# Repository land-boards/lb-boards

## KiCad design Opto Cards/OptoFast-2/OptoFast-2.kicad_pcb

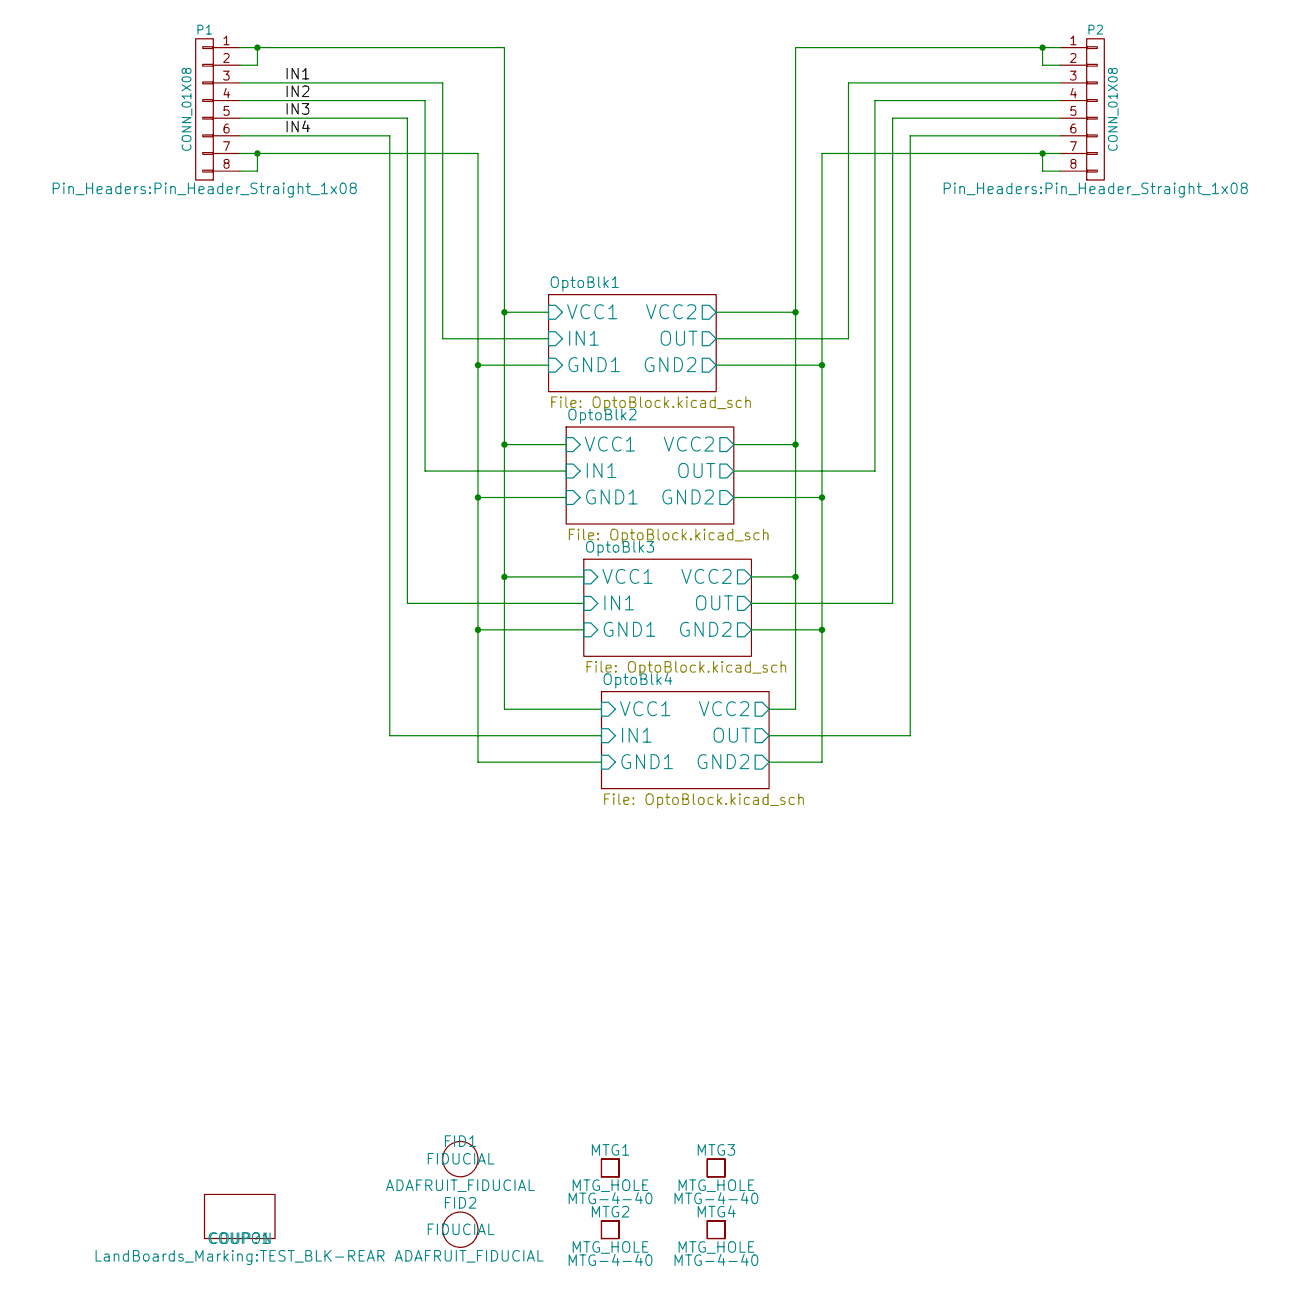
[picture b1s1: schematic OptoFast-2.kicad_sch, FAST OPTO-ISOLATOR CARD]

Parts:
COUP?1: COUPON; TEST_BLK-REAR
FID1, FID2: ADAFRUIT_FIDUCIAL; FIDUCIAL
MTG1, MTG2, MTG3, MTG4: MTG_HOLE; MTG-4-40
P1, P2: CONN_01X08; Pin_Header_Straight_1x08

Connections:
/IN1: P1.3; also elsewhere on the board
/IN2: P1.4; also elsewhere on the board
/IN3: P1.5; also elsewhere on the board
/IN4: P1.6; also elsewhere on the board
/OptoBlk1/GND1: P1.7, P1.8; also elsewhere on the board
/OptoBlk1/GND2: P2.7, P2.8; also elsewhere on the board
/OptoBlk1/OUT: P2.3; also elsewhere on the board
/OptoBlk1/VCC1: P1.1, P1.2; also elsewhere on the board
/OptoBlk1/VCC2: P2.1, P2.2; also elsewhere on the board
/OptoBlk2/OUT: P2.4; also elsewhere on the board
/OptoBlk3/OUT: P2.5; also elsewhere on the board
/OptoBlk4/OUT: P2.6; also elsewhere on the board

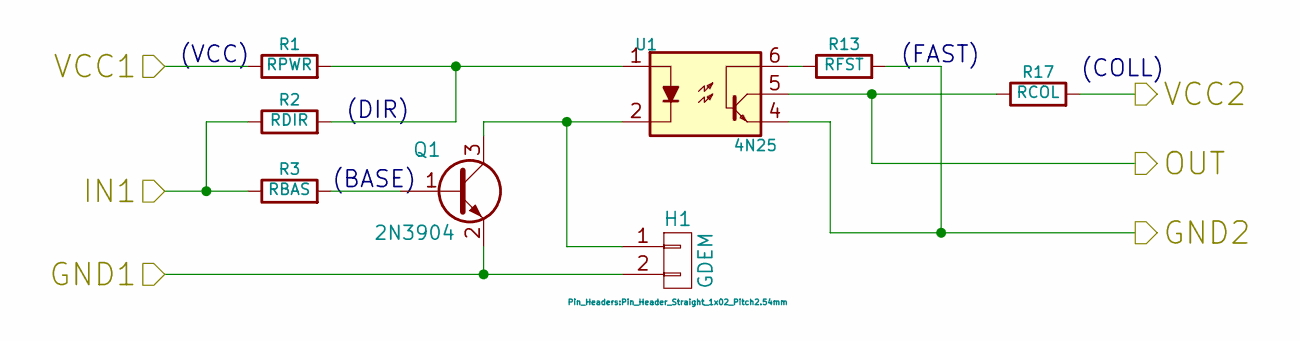
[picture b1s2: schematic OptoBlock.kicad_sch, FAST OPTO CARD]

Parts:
H1: GDEM; Pin_Header_Straight_1x02_Pitch2.54mm
Q1: 2N3904; SOT-23_Handsoldering
R1: RPWR; R_0805_HandSoldering
R2: RDIR; R_0805_HandSoldering
R3: RBAS; R_0805_HandSoldering
R13: RFST; R_0805_HandSoldering
R17: RCOL; R_0805_HandSoldering
U1: 4N25; DIP-6_W7.62mm_LongPads

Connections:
/IN1: R2.1, R3.1; also elsewhere on the board
/OptoBlk1/GND1: H1.2, Q1.2 (E); also elsewhere on the board
/OptoBlk1/GND2: R13.2, U1.4; also elsewhere on the board
/OptoBlk1/OUT: R17.1, U1.5; also elsewhere on the board
/OptoBlk1/VCC1: R1.1; also elsewhere on the board
/OptoBlk1/VCC2: R17.2; also elsewhere on the board
unnamed: H1.1, Q1.3 (C), U1.2
unnamed: Q1.1 (B), R3.2
unnamed: R1.2, R2.2, U1.1
unnamed: R13.1, U1.6

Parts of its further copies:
H2, H3, H4: GDEM; Pin_Header_Straight_1x02_Pitch2.54mm
Q2, Q3, Q4: 2N3904; SOT-23_Handsoldering
R4, R7, R10: RPWR; R_0805_HandSoldering
R5, R8, R11: RDIR; R_0805_HandSoldering
R6, R9, R12: RBAS; R_0805_HandSoldering
R14, R15, R16: RFST; R_0805_HandSoldering
R18, R19, R20: RCOL; R_0805_HandSoldering
U2, U3, U4: 4N25; DIP-6_W7.62mm_LongPads

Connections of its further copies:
/IN2: R5.1, R6.1; also elsewhere on the board
/IN3: R8.1, R9.1; also elsewhere on the board
/IN4: R11.1, R12.1; also elsewhere on the board
/OptoBlk1/GND1: H2.2, H3.2, H4.2, Q2.2 (E), Q3.2 (E), Q4.2 (E); also elsewhere on the board
/OptoBlk1/GND2: R14.2, R15.2, R16.2, U2.4, U3.4, U4.4; also elsewhere on the board
/OptoBlk1/VCC1: R4.1, R7.1, R10.1; also elsewhere on the board
/OptoBlk1/VCC2: R18.2, R19.2, R20.2; also elsewhere on the board
/OptoBlk2/OUT: R18.1, U2.5; also elsewhere on the board
/OptoBlk3/OUT: R19.1, U3.5; also elsewhere on the board
/OptoBlk4/OUT: R20.1, U4.5; also elsewhere on the board
unnamed: H2.1, Q2.3 (C), U2.2
unnamed: H3.1, Q3.3 (C), U3.2
unnamed: H4.1, Q4.3 (C), U4.2
unnamed: Q2.1 (B), R6.2
unnamed: Q3.1 (B), R9.2
unnamed: Q4.1 (B), R12.2
unnamed: R4.2, R5.2, U2.1
unnamed: R7.2, R8.2, U3.1
unnamed: R10.2, R11.2, U4.1
unnamed: R14.1, U2.6
unnamed: R15.1, U3.6
unnamed: R16.1, U4.6

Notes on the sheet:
(FAST)
(COLL)
(VCC)
(DIR)
(BASE)

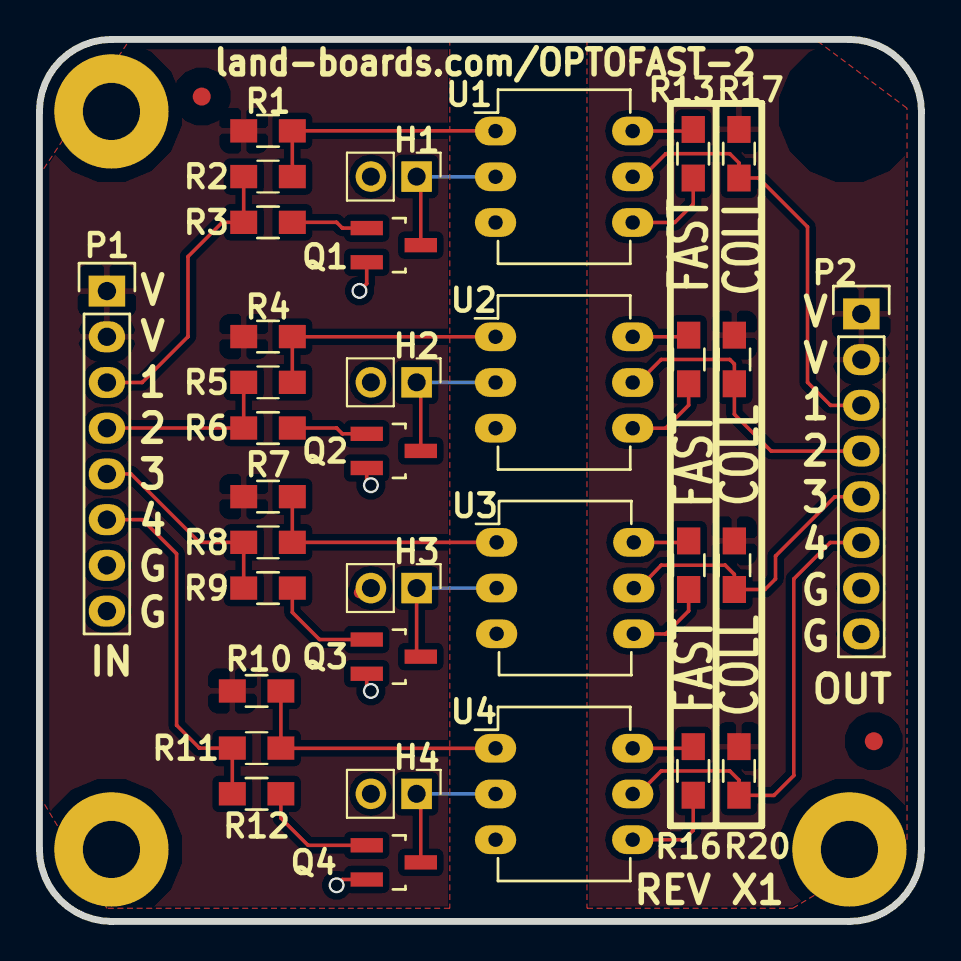
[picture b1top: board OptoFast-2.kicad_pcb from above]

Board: 2 copper layers, 49.0 x 49.0 mm, 40 parts (0 on the bottom side), 28 nets.

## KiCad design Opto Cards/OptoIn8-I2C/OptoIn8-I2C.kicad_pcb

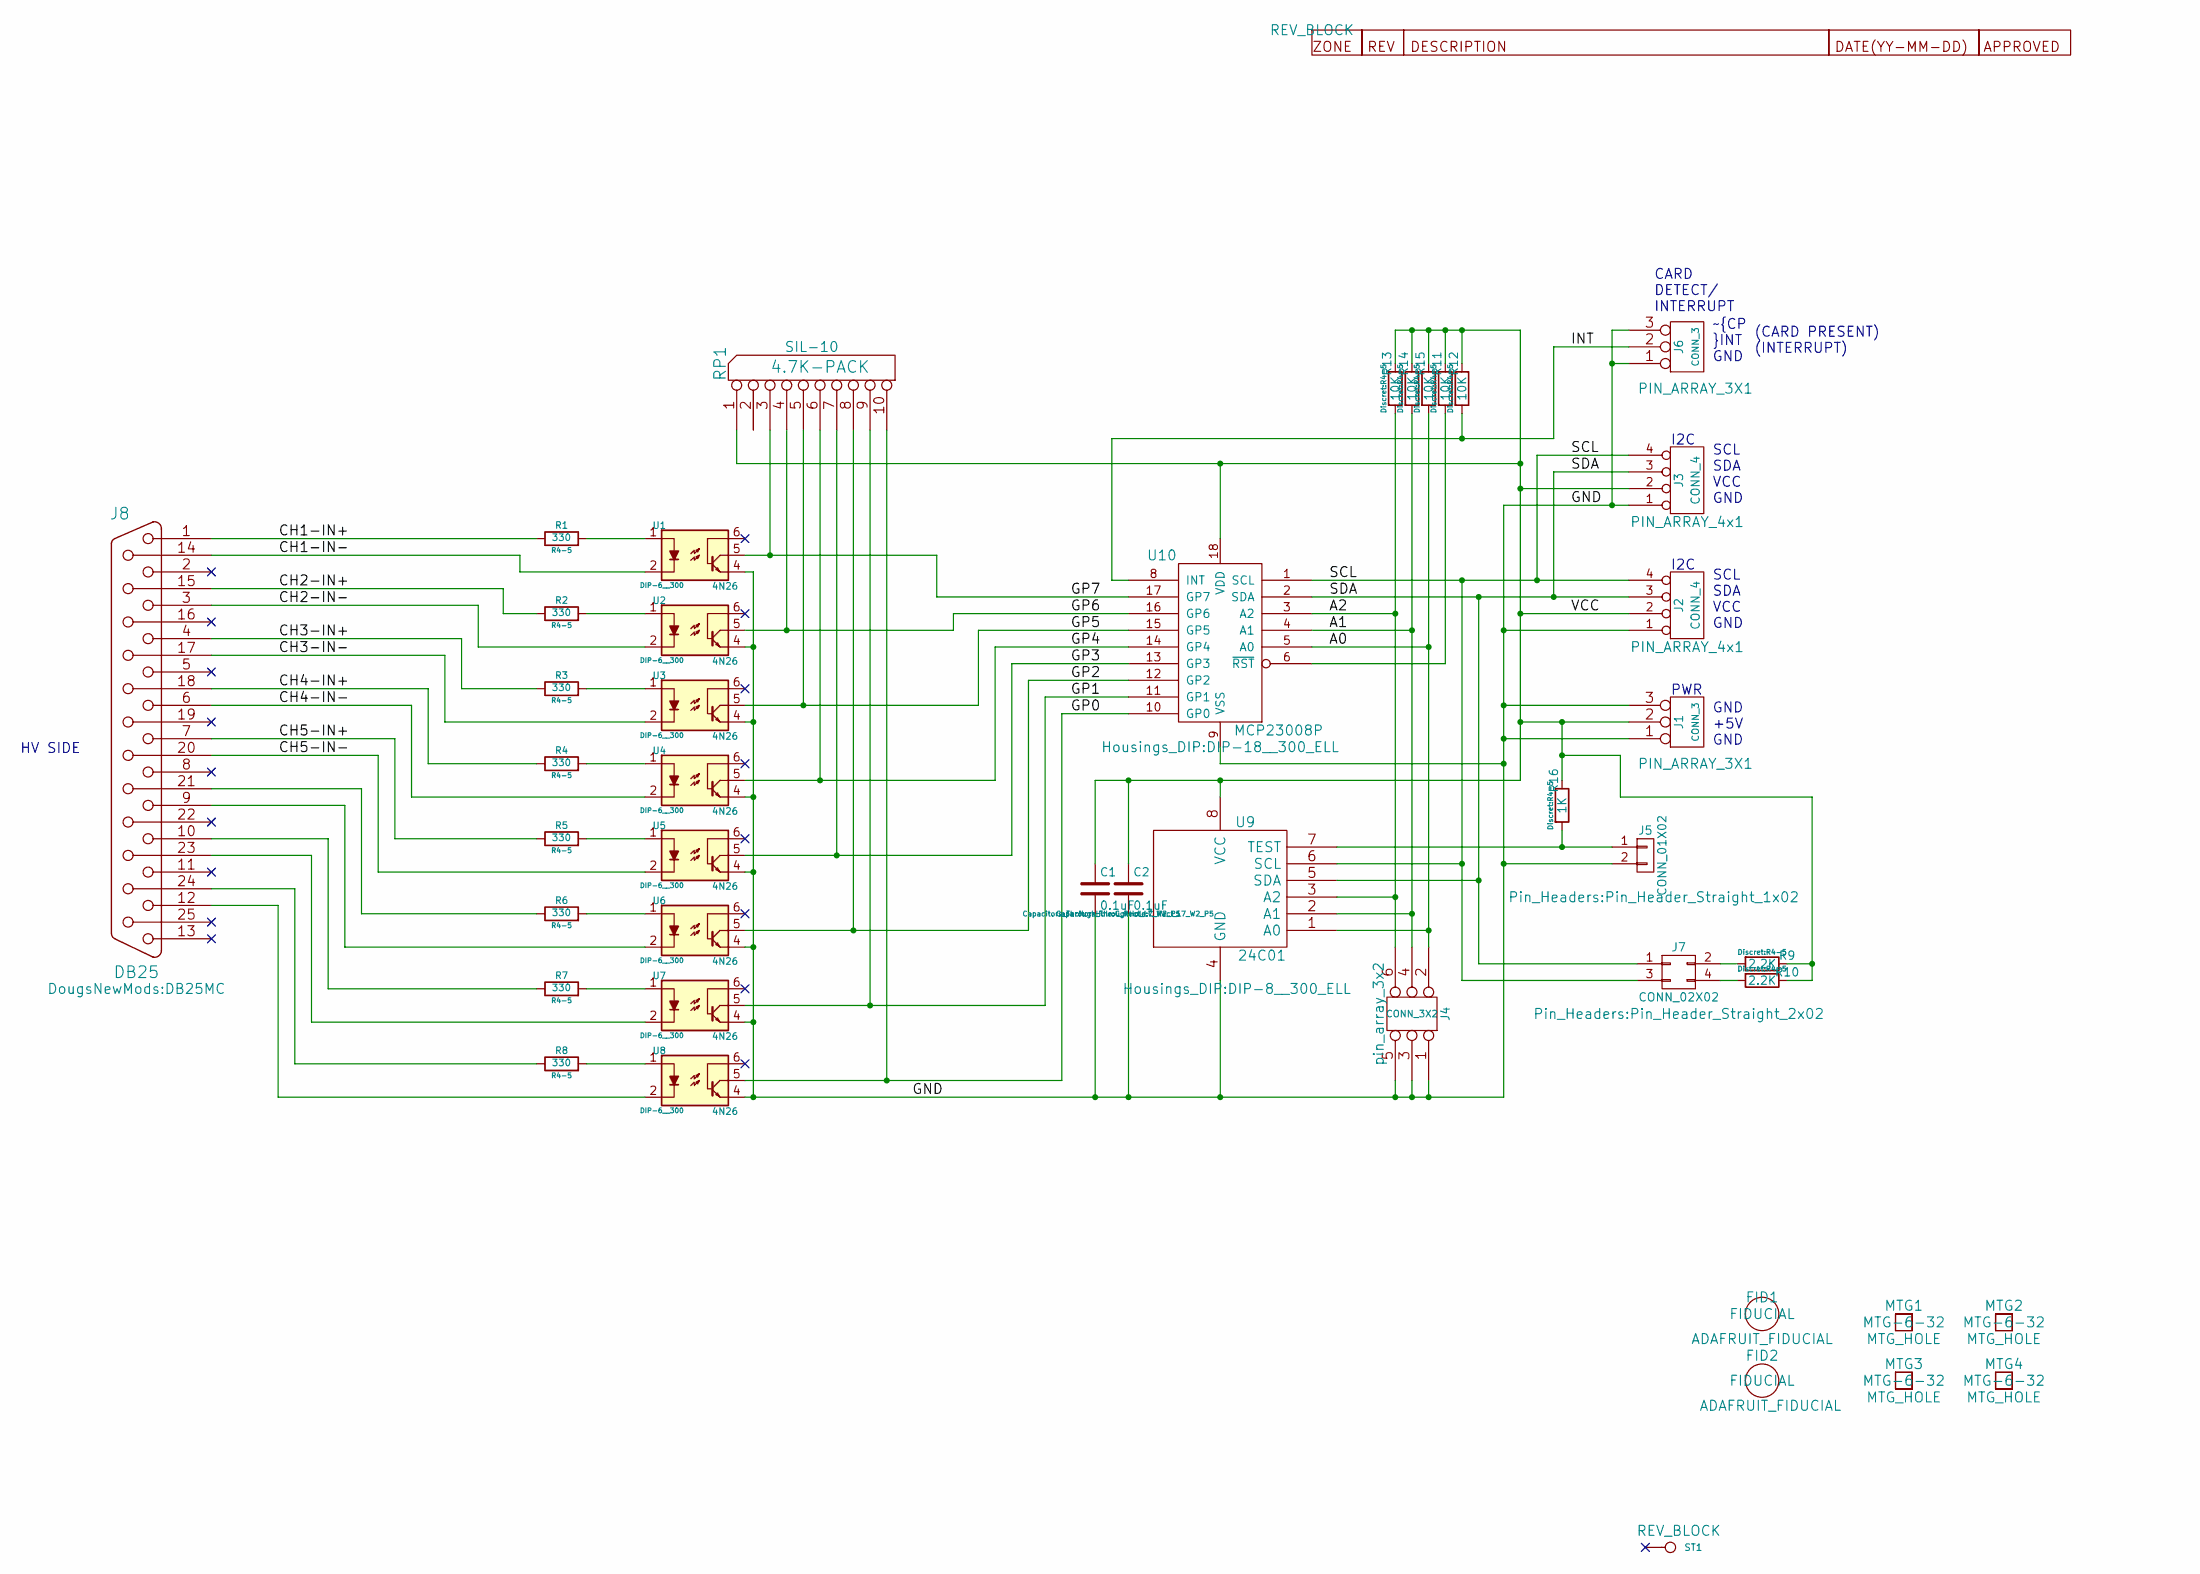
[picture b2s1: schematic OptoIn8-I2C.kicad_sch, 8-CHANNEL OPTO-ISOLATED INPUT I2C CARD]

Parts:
C1, C2: 0.1uF; C_Rect_L7_W2_P5
FID1, FID2: ADAFRUIT_FIDUCIAL; FIDUCIAL
J1, J6: CONN_3; PIN_ARRAY_3X1
J2, J3: CONN_4; PIN_ARRAY_4x1
J4: CONN_3X2; pin_array_3x2
J5: CONN_01X02; Pin_Header_Straight_1x02
J7: CONN_02X02; Pin_Header_Straight_2x02
J8: DB25; DB25MC
MTG1, MTG2, MTG3, MTG4: MTG_HOLE; MTG-6-32
R1, R2, R3, R4, R5, R6, R7, R8: 330; R4-5
R9, R10: 2.2K; R4-5
R11, R12, R13, R14, R15: 10K; R4-5
R16: 1K; R4-5
RP1: 4.7K-PACK; SIL-10; MfgPN 4610X-101-472LF
ST1: CONN_1; REV_BLOCK
ST2: REV-HIST; REV_BLOCK
U1, U2, U3, U4, U5, U6, U7, U8: 4N26; DIP-6__300
U9: 24C01; DIP-8__300_ELL
U10: MCP23008P; DIP-18__300_ELL

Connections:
/A0: J4.2, R15.2, U9.1 (A0), U10.5 (A0)
/A1: J4.4, R14.2, U9.2 (A1), U10.4 (A1)
/A2: J4.6, R13.2, U9.3 (A2), U10.3 (A2)
/CH1-IN+: J8.1, R1.1
/CH1-IN-: J8.14, U1.2
/CH2-IN+: J8.15, R2.1
/CH2-IN-: J8.3, U2.2
/CH3-IN+: J8.4, R3.1
/CH3-IN-: J8.17, U3.2
/CH4-IN+: J8.18, R4.1
/CH4-IN-: J8.6, U4.2
/CH5-IN+: J8.7, R5.1
/CH5-IN-: J8.20, U5.2
/GND: C1.2, C2.2, J1.1, J1.3, J2.1, J3.1, J4.1, J4.3, J4.5, J5.2, J6.1, J6.3, U1.4, U2.4, U3.4, U4.4, U5.4, U6.4, U7.4, U8.4, U9.4 (GND), U10.9 (VSS)
/GP0: RP1.10, U8.5, U10.10 (GP0)
/GP1: RP1.9, U7.5, U10.11 (GP1)
/GP2: RP1.8, U6.5, U10.12 (GP2)
/GP3: RP1.7, U5.5, U10.13 (GP3)
/GP4: RP1.6, U4.5, U10.14 (GP4)
/GP5: RP1.5, U3.5, U10.15 (GP5)
/GP6: RP1.4, U2.5, U10.16 (GP6)
/GP7: RP1.3, U1.5, U10.17 (GP7)
/INT: J6.2 (PM), R12.2, U10.8 (INT)
/SCL: J2.4, J3.4, J7.3, U9.6 (SCL), U10.1 (SCL)
/SDA: J2.3, J3.3, J7.1, U9.5 (SDA), U10.2 (SDA)
/VCC: C1.1, C2.1, J1.2 (PM), J2.2, J3.2, R9.1, R10.1, R11.1, R12.1, R13.1, R14.1, R15.1, R16.1, RP1.1 (COM), U9.8 (VCC), U10.18 (VDD)
unnamed: J5.1, R16.2, U9.7 (TEST)
unnamed: J7.2, R9.2
unnamed: J7.4, R10.2
unnamed: J8.9, U6.2
unnamed: J8.10, R7.1
unnamed: J8.12, U8.2
unnamed: J8.21, R6.1
unnamed: J8.23, U7.2
unnamed: J8.24, R8.1
unnamed: R1.2, U1.1
unnamed: R2.2, U2.1
unnamed: R3.2, U3.1
unnamed: R4.2, U4.1
unnamed: R5.2, U5.1
unnamed: R6.2, U6.1
unnamed: R7.2, U7.1
unnamed: R8.2, U8.1
unnamed: R11.2, U10.6 (~RST)

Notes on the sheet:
I2C
(CARD PRESENT) (INTERRUPT)
GND +5V GND
HV SIDE
CARD DETECT/ INTERRUPT
SCL SDA VCC GND
~{CP }INT GND
PWR

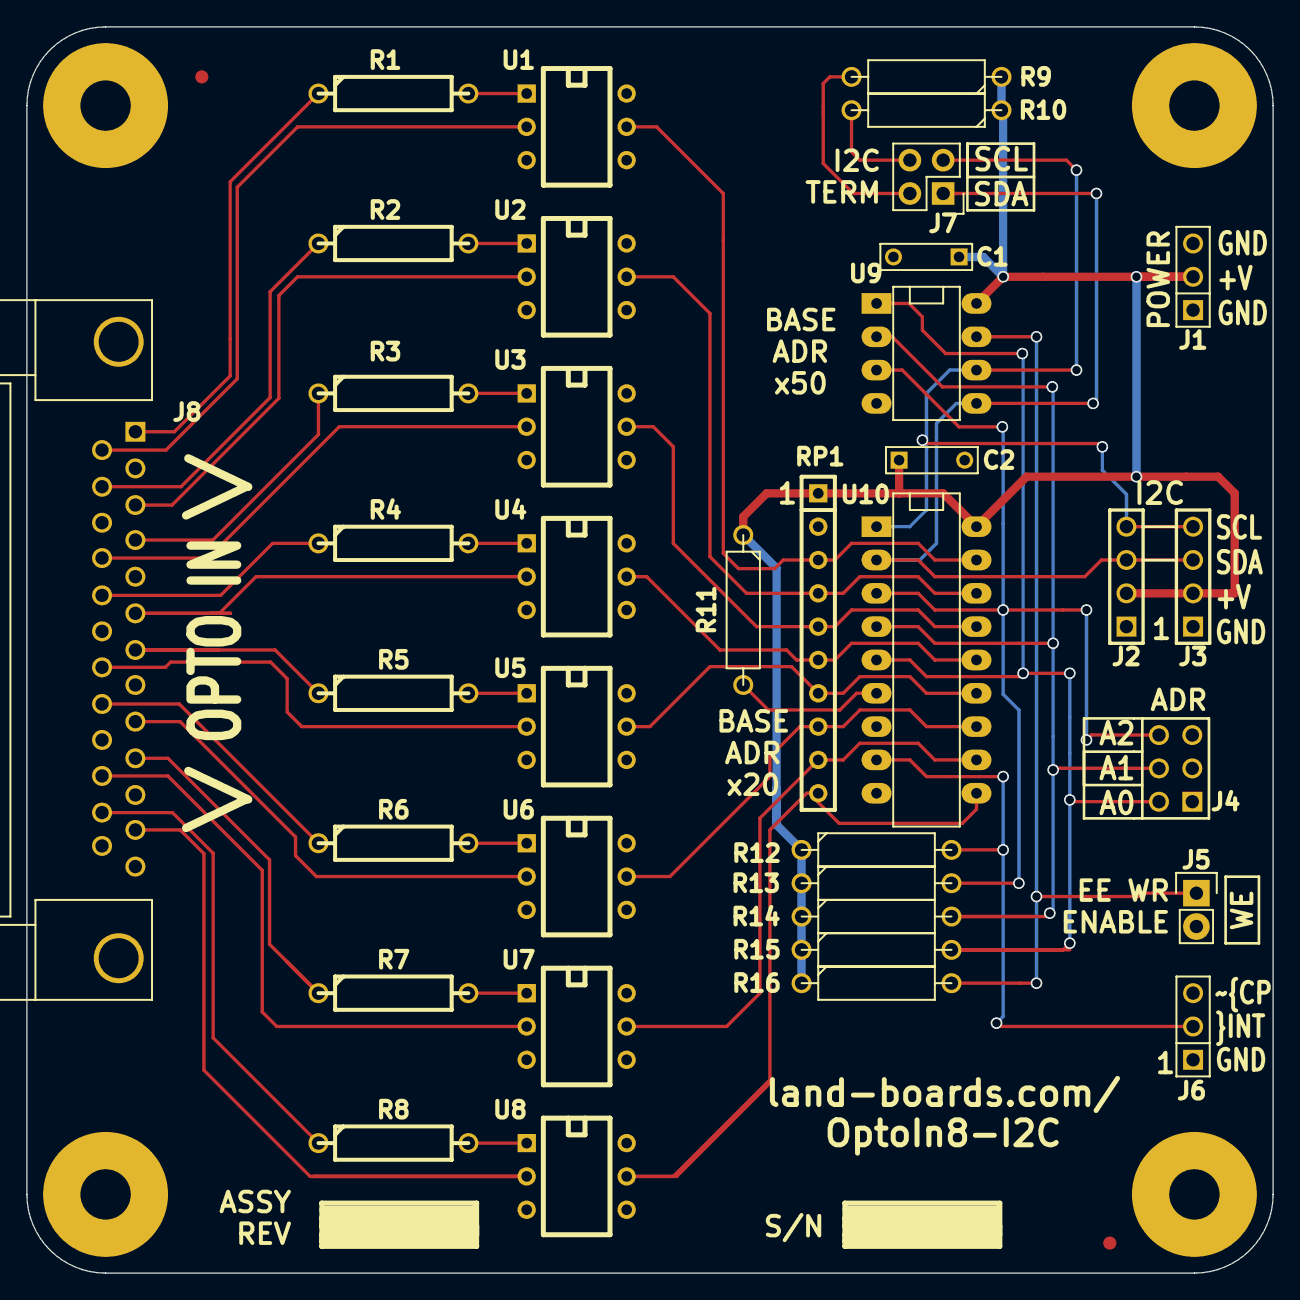
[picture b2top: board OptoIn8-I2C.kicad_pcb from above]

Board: 2 copper layers, 95.0 x 95.0 mm, 46 parts (0 on the bottom side), 44 nets.

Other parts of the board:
TESTED: VAL**; TEST_BLK-REAR

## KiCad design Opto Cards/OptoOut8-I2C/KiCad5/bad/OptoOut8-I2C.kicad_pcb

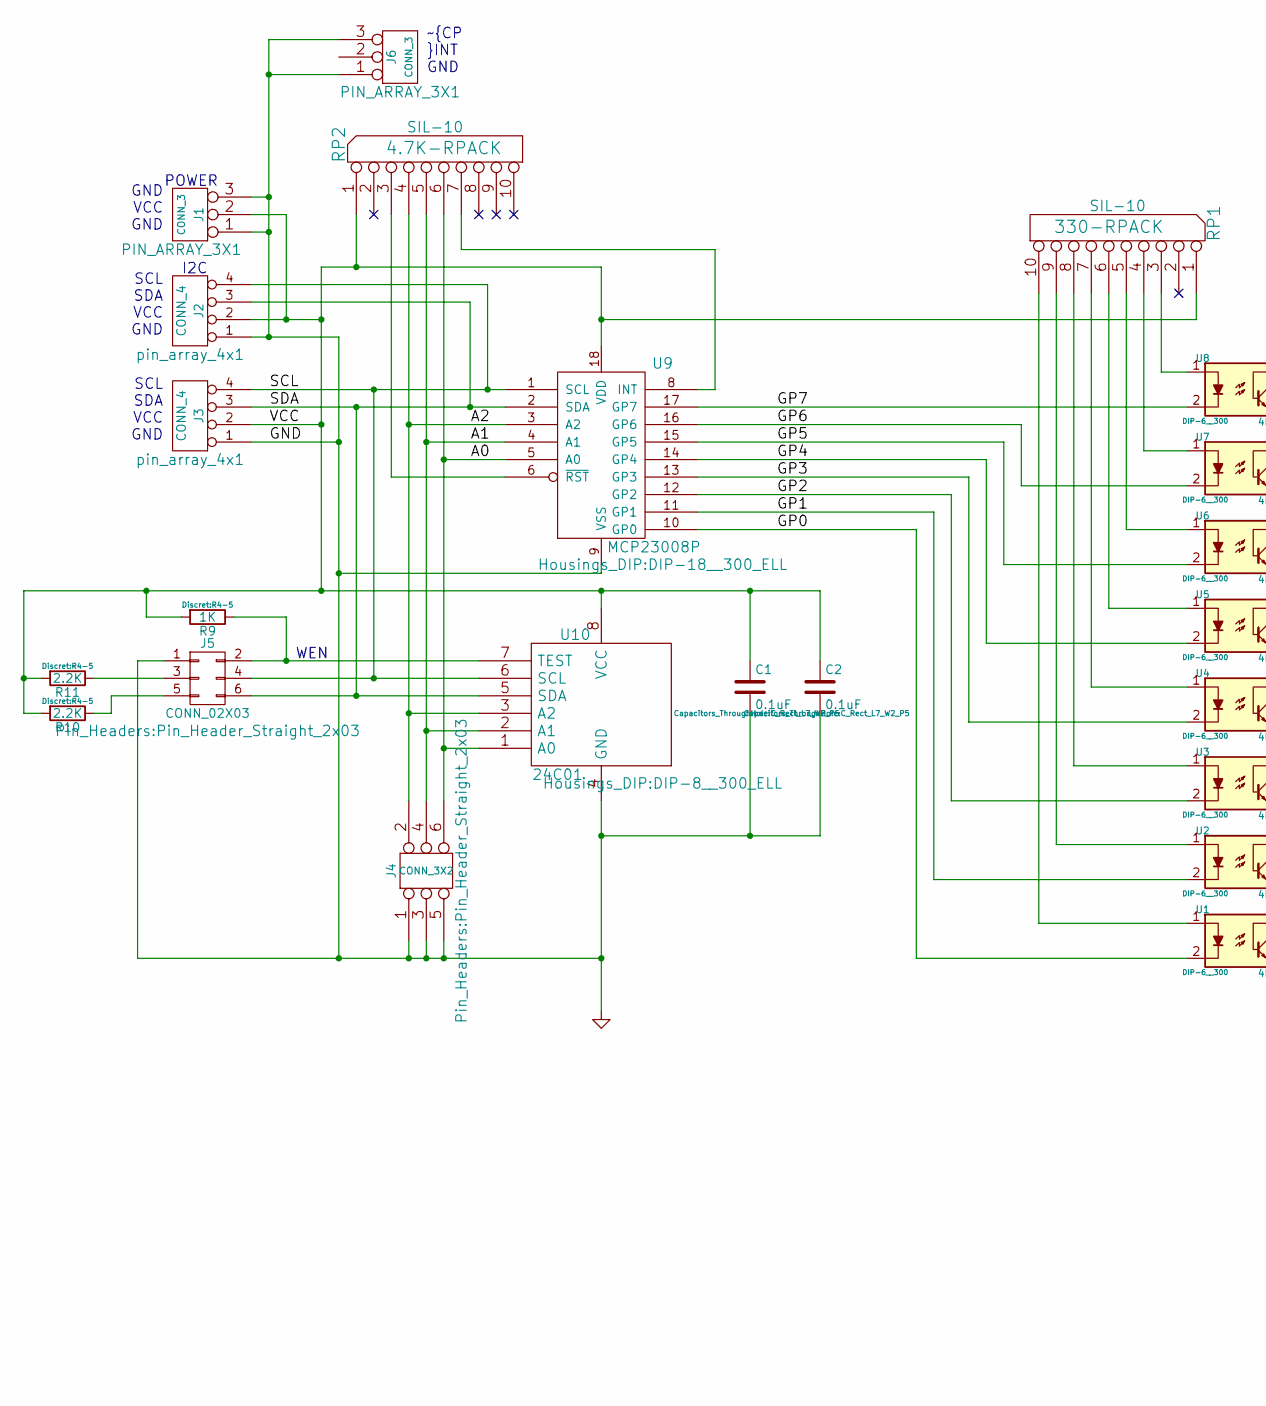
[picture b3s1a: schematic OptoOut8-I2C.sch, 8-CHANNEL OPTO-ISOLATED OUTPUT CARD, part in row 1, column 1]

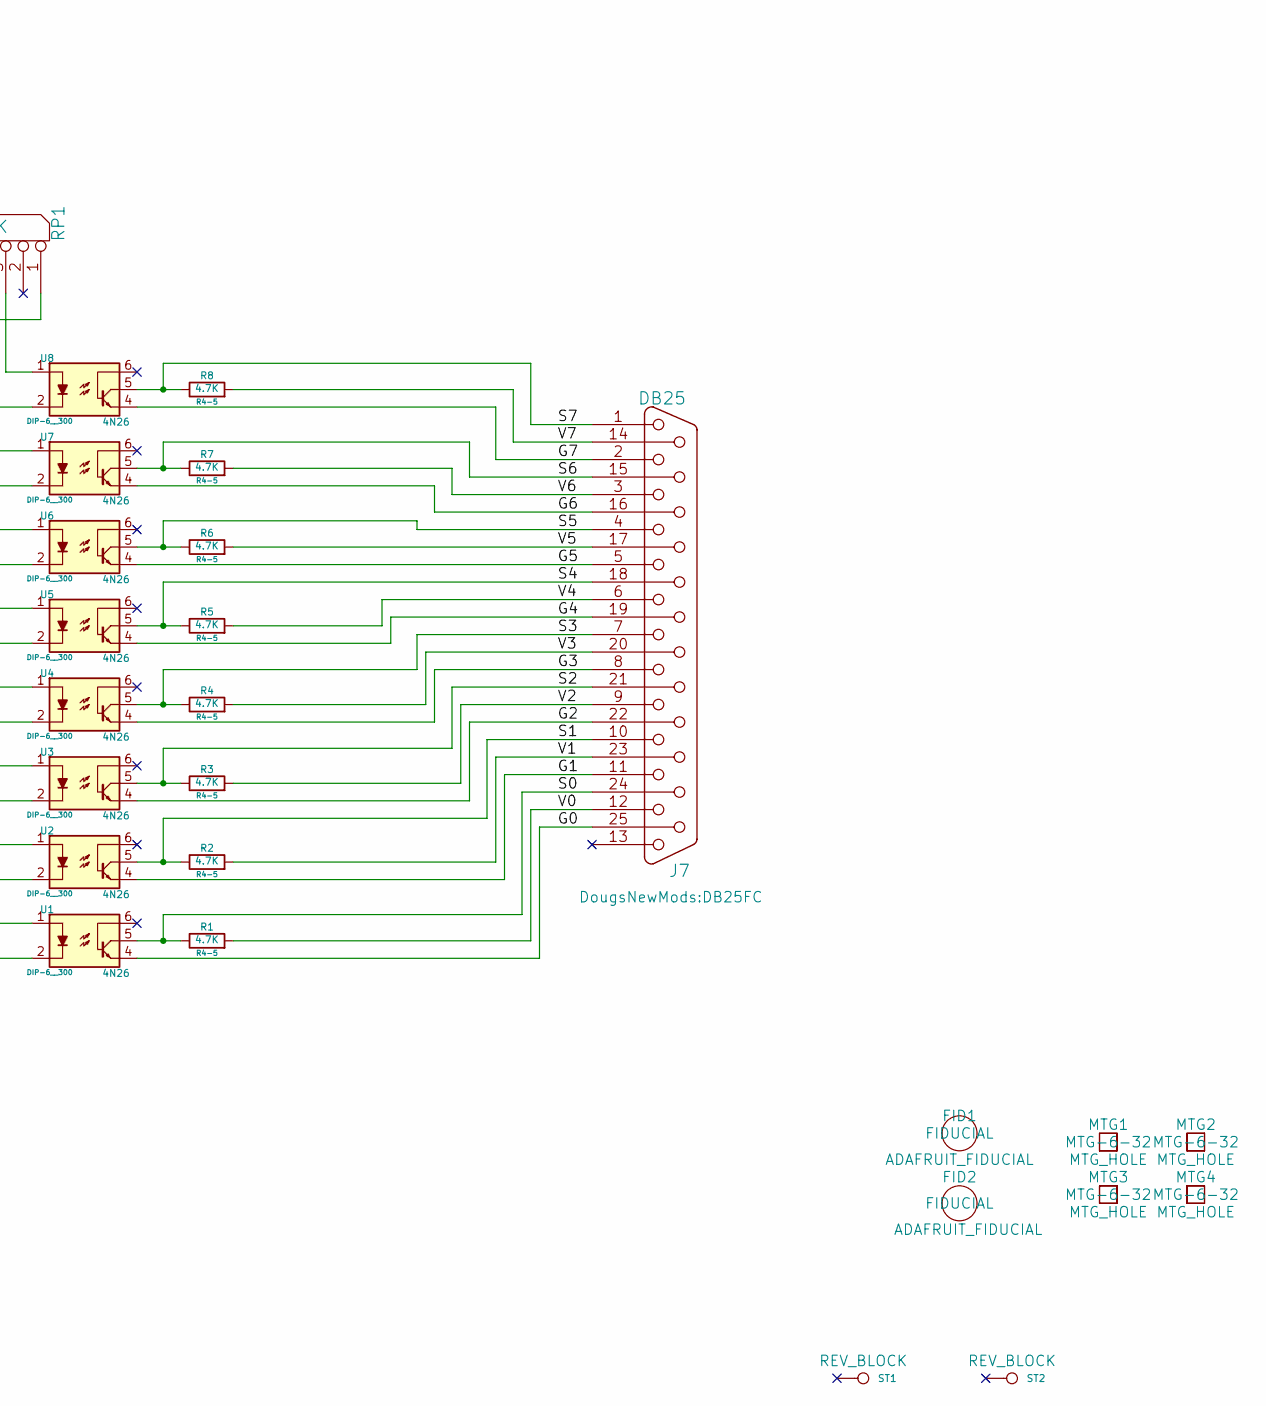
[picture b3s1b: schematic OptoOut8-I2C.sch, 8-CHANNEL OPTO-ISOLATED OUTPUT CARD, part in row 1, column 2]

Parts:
C1, C2: 0.1uF; C_Rect_L7_W2_P5
FID1, FID2: ADAFRUIT_FIDUCIAL; FIDUCIAL
J1, J6: CONN_3; PIN_ARRAY_3X1
J2, J3: CONN_4; pin_array_4x1
J4: CONN_3X2; Pin_Header_Straight_2x03
J5: CONN_02X03; Pin_Header_Straight_2x03
J7: DB25; DB25FC
MTG1, MTG2, MTG3, MTG4: MTG_HOLE; MTG-6-32
R1, R2, R3, R4, R5, R6, R7, R8: 4.7K; R4-5
R9: 1K; R4-5
R10, R11: 2.2K; R4-5
RP1: 330-RPACK; SIL-10
RP2: 4.7K-RPACK; SIL-10
ST1, ST2: CONN_1; REV_BLOCK
U1, U2, U3, U4, U5, U6, U7, U8: 4N26; DIP-6__300
U9: MCP23008P; DIP-18__300_ELL
U10: 24C01; DIP-8__300_ELL

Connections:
/A0: J4.6, RP2.6, U9.5 (A0), U10.1 (A0)
/A1: J4.4, RP2.5, U9.4 (A1), U10.2 (A1)
/A2: J4.2, RP2.4, U9.3 (A2), U10.3 (A2)
/G0: J7.25, U1.4
/G1: J7.11, U2.4
/G2: J7.22, U3.4
/G3: J7.8, U4.4
/G4: J7.19, U5.4
/G5: J7.5, U6.4
/G6: J7.16, U7.4
/G7: J7.2, U8.4
/S0: J7.24, R1.1, U1.5
/S1: J7.10, R2.1, U2.5
/S2: J7.21, R3.1, U3.5
/S3: J7.7, R4.1, U4.5
/S4: J7.18, R5.1, U5.5
/S5: J7.4, R6.1, U6.5
/S6: J7.15, R7.1, U7.5
/S7: J7.1, R8.1, U8.5
/SCL: J2.4, J3.4, J5.4, U9.1 (SCL), U10.6 (SCL)
/SDA: J2.3, J3.3, J5.6, U9.2 (SDA), U10.5 (SDA)
/V0: J7.12, R1.2
/V1: J7.23, R2.2
/V2: J7.9, R3.2
/V3: J7.20, R4.2
/V4: J7.6, R5.2
/V5: J7.17, R6.2
/V6: J7.3, R7.2
/V7: J7.14, R8.2
/VCC: C1.1, C2.1, J1.2 (PM), J2.2, J3.2, R9.2, R10.2, R11.2, RP1.1 (COM), RP2.1 (COM), U9.18 (VDD), U10.8 (VCC)
GND: C1.2, C2.2, J1.1, J1.3, J2.1, J3.1, J4.1, J4.3, J4.5, J5.1, J6.1, J6.3, U9.9 (VSS), U10.4 (GND)
unnamed: J5.2, R9.1, U10.7 (TEST)
unnamed: J5.3, R11.1
unnamed: J5.5, R10.1
unnamed: RP1.3, U8.1
unnamed: RP1.4, U7.1
unnamed: RP1.5, U6.1
unnamed: RP1.6, U5.1
unnamed: RP1.7, U4.1
unnamed: RP1.8, U3.1
unnamed: RP1.9, U2.1
unnamed: RP1.10, U1.1
unnamed: RP2.3, U9.6 (~RST)
unnamed: RP2.7, U9.8 (INT)
unnamed: U1.2, U9.10 (GP0)
unnamed: U2.2, U9.11 (GP1)
unnamed: U3.2, U9.12 (GP2)
unnamed: U4.2, U9.13 (GP3)
unnamed: U5.2, U9.14 (GP4)
unnamed: U6.2, U9.15 (GP5)
unnamed: U7.2, U9.16 (GP6)
unnamed: U8.2, U9.17 (GP7)

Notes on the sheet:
SCL SDA VCC GND
GND VCC GND
~CP ~INT GND
POWER
I2C
WEN

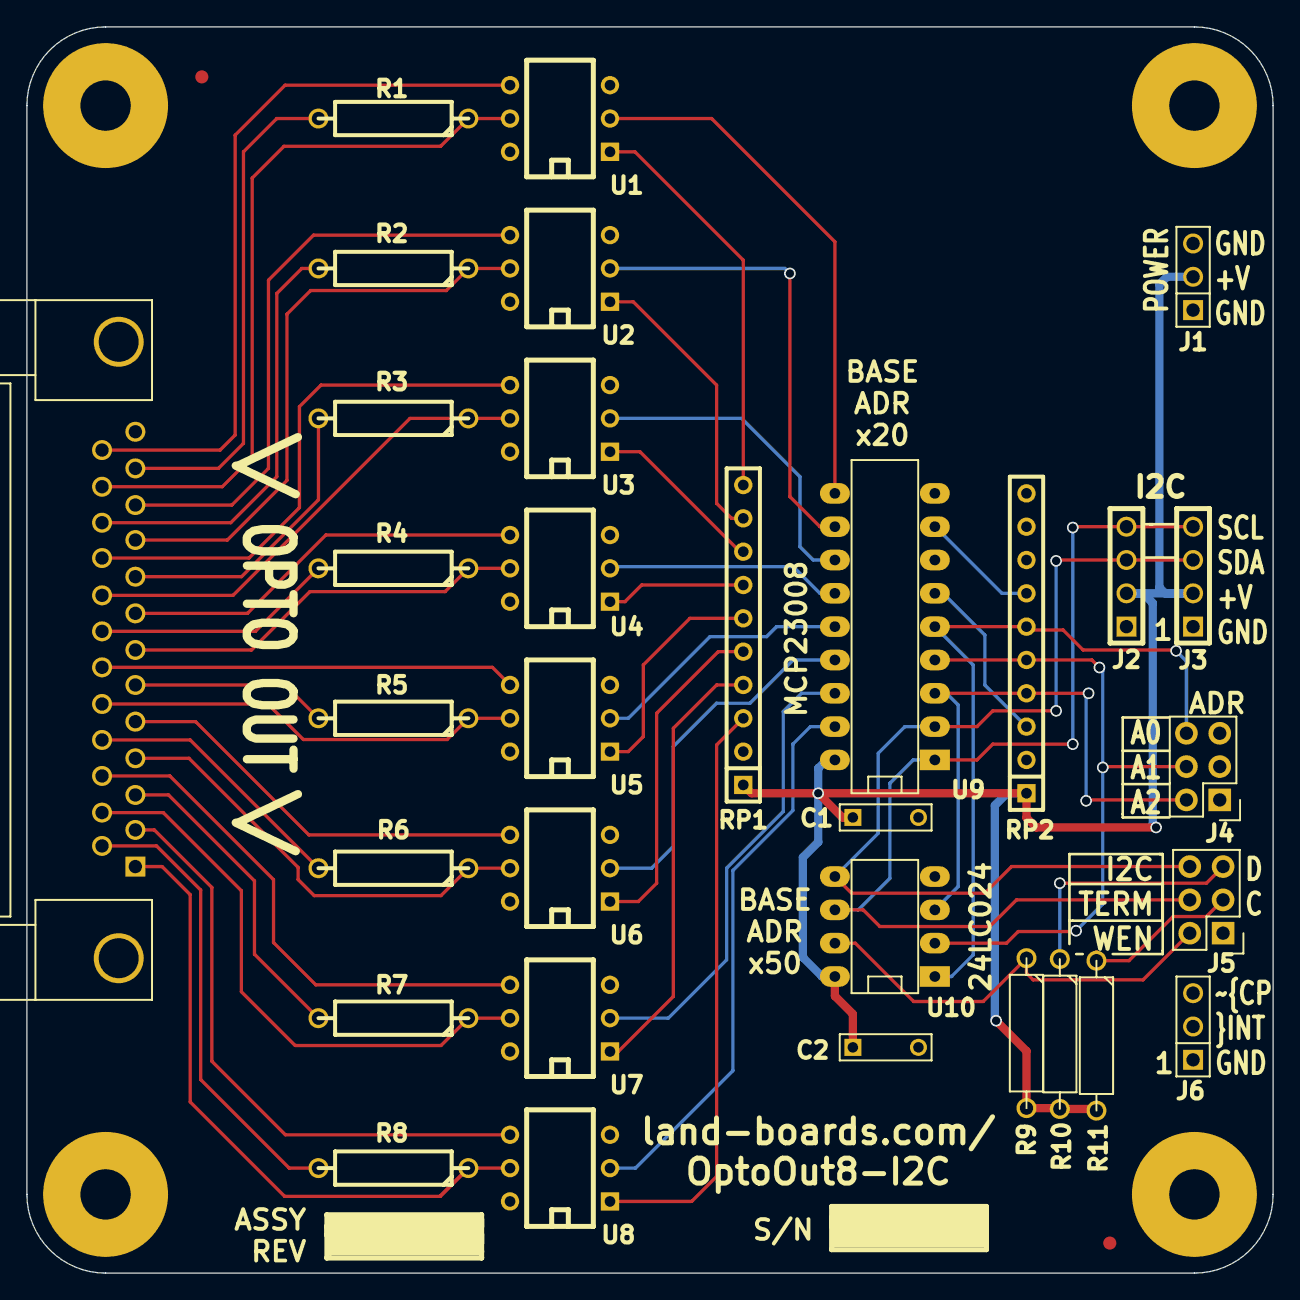
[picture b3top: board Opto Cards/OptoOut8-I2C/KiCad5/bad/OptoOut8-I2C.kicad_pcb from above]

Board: 2 copper layers, 95.0 x 95.0 mm, 40 parts (0 on the bottom side), 52 nets.

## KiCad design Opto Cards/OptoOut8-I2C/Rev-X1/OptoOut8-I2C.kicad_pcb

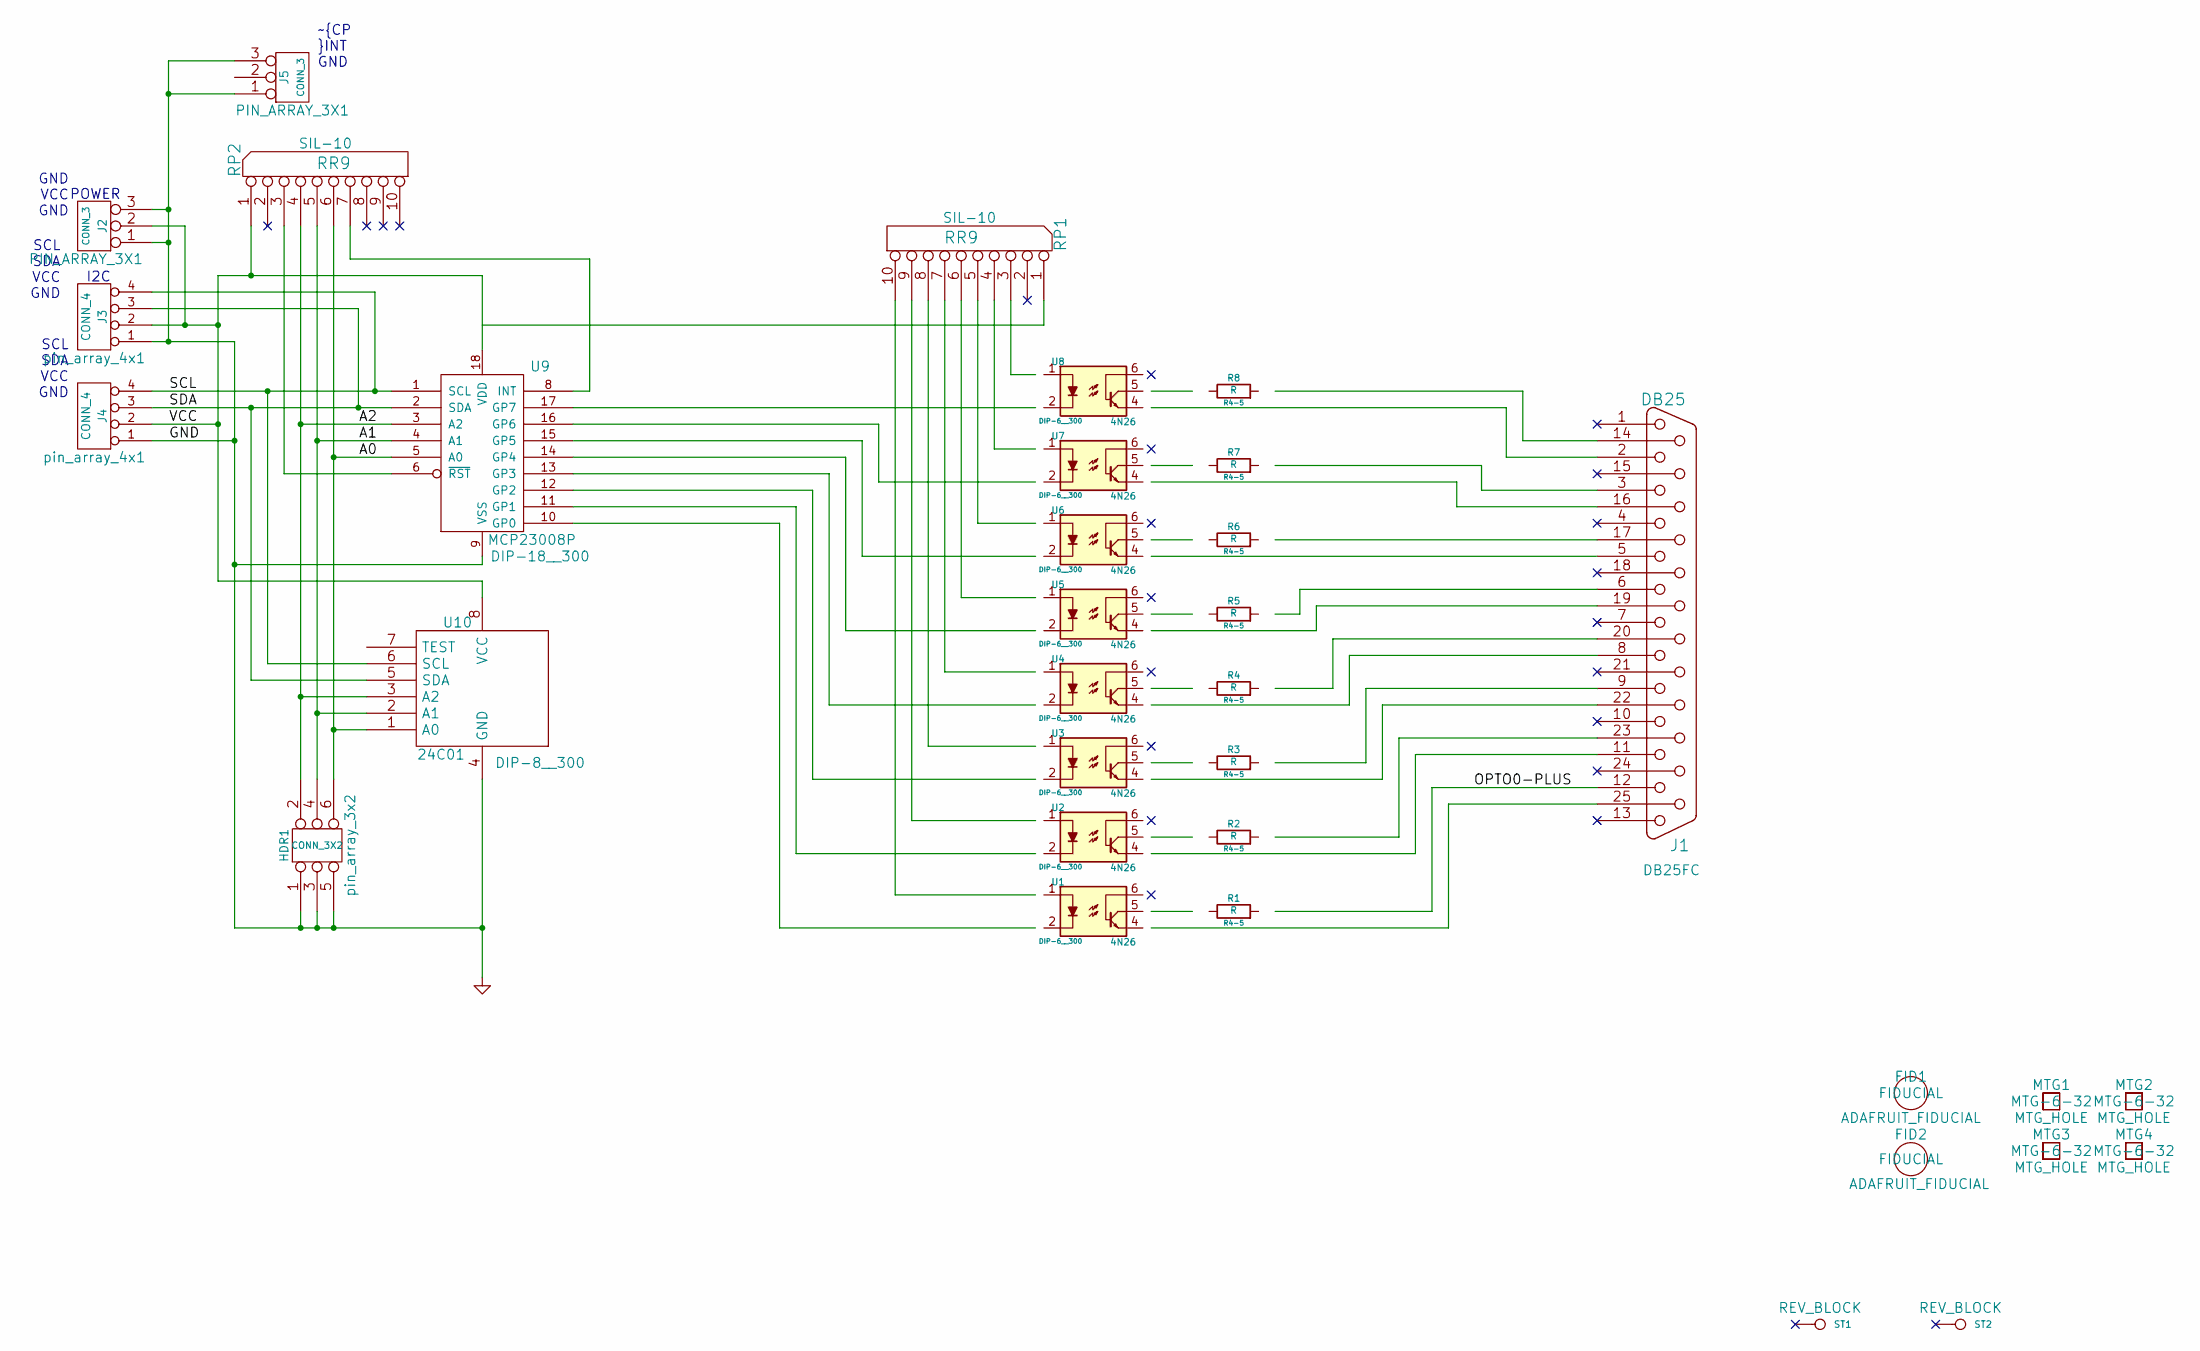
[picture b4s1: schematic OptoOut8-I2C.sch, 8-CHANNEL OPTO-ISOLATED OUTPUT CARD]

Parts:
FID1, FID2: ADAFRUIT_FIDUCIAL; FIDUCIAL
HDR1: CONN_3X2; pin_array_3x2
J1: DB25; DB25FC
J2, J5: CONN_3; PIN_ARRAY_3X1
J3, J4: CONN_4; pin_array_4x1
MTG1, MTG2, MTG3, MTG4: MTG_HOLE; MTG-6-32
R1, R2, R3, R4, R5, R6, R7, R8: R; R4-5
RP1, RP2: RR9; SIL-10
ST1, ST2: CONN_1; REV_BLOCK
U1, U2, U3, U4, U5, U6, U7, U8: 4N26; DIP-6__300
U9: MCP23008P; DIP-18__300
U10: 24C01; DIP-8__300

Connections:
/A0: HDR1.6, RP2.6, U9.5 (A0), U10.1 (A0)
/A1: HDR1.4, RP2.5, U9.4 (A1), U10.2 (A1)
/A2: HDR1.2, RP2.4, U9.3 (A2), U10.3 (A2)
/SCL: J3.4, J4.4, U9.1 (SCL), U10.6 (SCL)
/SDA: J3.3, J4.3, U9.2 (SDA), U10.5 (SDA)
/VCC: J2.2 (PM), J3.2, J4.2, RP2.1 (COM), U9.18 (VDD), U10.8 (VCC)
GND: HDR1.1, HDR1.3, HDR1.5, J2.1, J2.3, J3.1, J4.1, J5.1, J5.3, U9.9 (VSS), U10.4 (GND)
unnamed: RP1.3, U8.1
unnamed: U8.2, U9.17 (GP7)
unnamed: RP2.7, U9.8 (INT)
unnamed: RP2.3, U9.6 (~RST)
unnamed: RP1.9, U2.1
unnamed: U5.2, U9.14 (GP4)
unnamed: U6.2, U9.15 (GP5)
unnamed: U7.2, U9.16 (GP6)
unnamed: RP1.10, U1.1
unnamed: RP1.8, U3.1
unnamed: RP1.7, U4.1
unnamed: RP1.6, U5.1
unnamed: RP1.5, U6.1
unnamed: RP1.4, U7.1
unnamed: U1.2, U9.10 (GP0)
unnamed: U2.2, U9.11 (GP1)
unnamed: U3.2, U9.12 (GP2)
unnamed: U4.2, U9.13 (GP3)
unnamed: J1.22, U3.4
unnamed: J1.23, R2.2
unnamed: J1.12, R1.2
unnamed: J1.11, U2.4
unnamed: J1.20, R4.2
unnamed: J1.9, R3.2
unnamed: J1.8, U4.4
unnamed: J1.6, R5.2
unnamed: J1.14, R8.2
unnamed: J1.17, R6.2
unnamed: J1.3, R7.2
unnamed: R5.1, U5.5
unnamed: J1.19, U5.4
unnamed: R6.1, U6.5
unnamed: J1.5, U6.4
unnamed: R7.1, U7.5
unnamed: J1.16, U7.4
unnamed: R8.1, U8.5
unnamed: J1.2, U8.4
unnamed: R1.1, U1.5
unnamed: J1.25, U1.4
unnamed: R2.1, U2.5
unnamed: R3.1, U3.5
unnamed: R4.1, U4.5

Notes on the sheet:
SCL SDA VCC GND
GND VCC GND
~CP ~INT GND
POWER
I2C
